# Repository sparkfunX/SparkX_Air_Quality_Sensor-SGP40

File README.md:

SparkX Air Quality Sensor - SGP40 (Qwiic)
========================================

[*SparkX Air Quality Sensor - SGP40 (Qwiic) (SPX-17729)*](https://www.sparkfun.com/products/17729)

The SGP40 is a digital gas sensor designed for easy integration into air purifiers or demand-controlled ventilation systems.
Sensirion’s CMOSens® technology offers a complete, easy to use sensor system on a single chip featuring a digital
I<sup>2</sup>C interface and a temperature controlled micro hotplate, providing a humidity compensated VOC based indoor air quality signal.
The output signal can be directly processed by Sensirion’s powerful VOC Algorithm to translate the raw signal into a VOC Index as a robust
measure for indoor air quality. The VOC Algorithm automatically adapts to the environment the sensor is exposed to. Both sensing element and
VOC Algorithm feature an unmatched robustness against contaminating gases present in real world applications enabling a unique long term
stability as well as low drift and device to device variation.

Repository Contents
-------------------
* **/Documents** - datasheets etc.
* **/Hardware** - Eagle design files (.brd, .sch)

Documentation
--------------
* **[SGP40 Arduino Library](https://github.com/sparkfun/SparkFun_SGP40_Arduino_Library)** - Arduino library for the SparkFun Air Quality Sensor - SGP40.
* **[Hookup Guide]()** - Basic hookup guide for the SparkFun Air Quality Sensor - SGP40.

Product Versions
----------------
* [SPX-17729](https://www.sparkfun.com/products/17729) - Original SparkX Release.

License Information
-------------------

This product is _**open source**_!

Please review the LICENSE.md file for license information.

If you have any questions or concerns on licensing, please contact technical support on our [SparkFun forums](https://forum.sparkfun.com/viewforum.php?f=152).

Distributed as-is; no warranty is given.

- Your friends at SparkFun.

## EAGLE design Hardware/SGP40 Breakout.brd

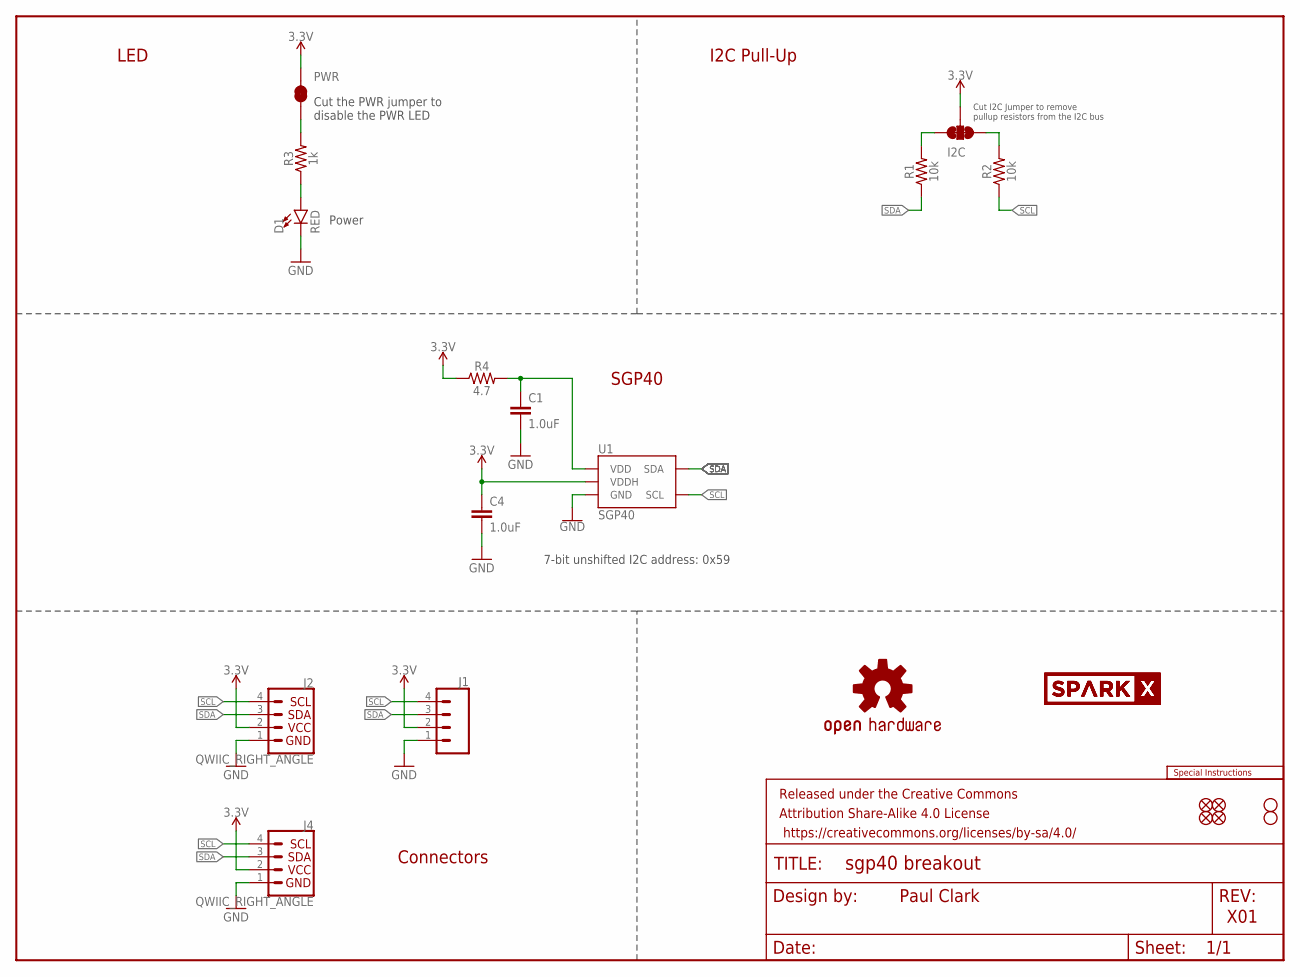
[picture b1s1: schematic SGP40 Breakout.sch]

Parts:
C1, C4: 1.0uF; 0603
D1: RED; LED-0603
FRAME1: FRAME-LETTER; CREATIVE_COMMONS
I2C: JUMPER-SMT_3_2-NC_TRACE_SILK; SMT-JUMPER_3_2-NC_TRACE_SILK
J1: CONN_041X04_NO_SILK; 1X04_NO_SILK
J2, J4: QWIIC_RIGHT_ANGLE; JST04_1MM_RA
JP1, JP2, JP5, JP6: FIDUCIALUFIDUCIAL; MICRO-FIDUCIAL
JP3, JP4: STAND-OFF
LOGO1: SPECIAL_INSTRUCTIONS-ORDERING; ORDERING_INSTRUCTIONS
LOGO5: OSHW-LOGOS; OSHW-LOGO-S
PWR: JUMPER-SMT_2_NC_TRACE_SILK; SMT-JUMPER_2_NC_TRACE_SILK
R1, R2: 10k; 0603
R3: 1k; 0603
R4: 4.7; 0603
U1: SGP40
U$10, U$18: SPARKX-LOGO3; SPARKX-SMALL

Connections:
3.3V: C4.1, I2C.2, J1.2, J2.2, J4.2, PWR.2, R4.1, U1.5 (VDDH)
GND: C1.2, C4.2, D1.C, J1.1, J2.1, J4.1, U1.2 (GND), U1.4 (GND), U1.DIEPAD (GND)
unnamed: PWR.1, R3.2
unnamed: I2C.3, R1.2
unnamed: D1.A, R3.1
unnamed: I2C.1, R2.2
unnamed: C1.1, R4.2, U1.1 (VDD)
SCL: J1.4, J2.4, J4.4, R2.1, U1.6 (SCL)
SDA: J1.3, J2.3, J4.3, R1.1, U1.3 (SDA)

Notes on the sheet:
Paul Clark
X01
7-bit unshifted I2C address: 0x59
Power
I2C Pull-Up
SGP40
Connectors
Cut the PWR jumper to disable the PWR LED
Cut I2C Jumper to remove pullup resistors from the I2C bus
LED

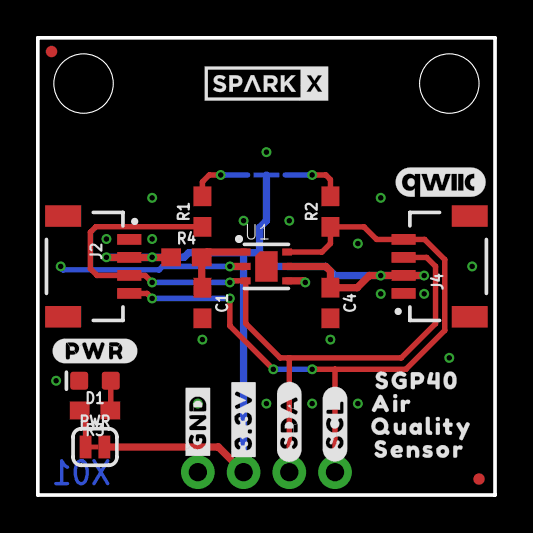
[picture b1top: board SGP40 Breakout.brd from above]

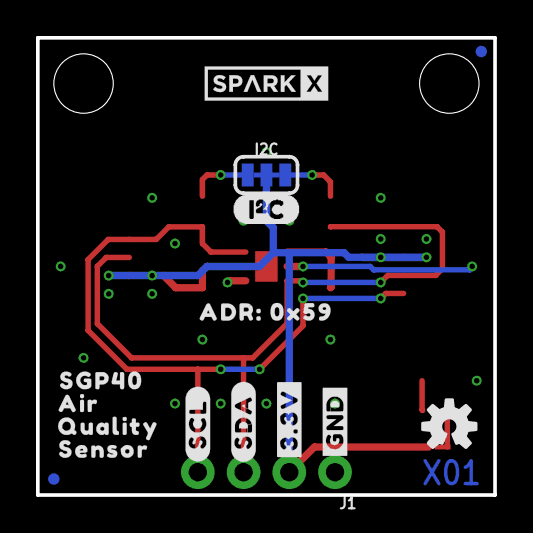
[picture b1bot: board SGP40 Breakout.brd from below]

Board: 4 copper layers, 25.4 x 25.4 mm, 44 parts (16 on the bottom side), 9 nets.

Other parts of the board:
U$1, U$33: #GND#0
U$2, U$34: #3#3V#0
U$3, U$35: #SDA#0
U$4, U$36: #SCL#0
U$15: I2C
U$16: QWIIC_5MM
U$19, U$20: SGP400
U$23, U$24: AIR0
U$25, U$28: QUALITY0
U$29, U$30: SENSOR0
U$31: ADR#_0X590
U$32: #PWR#0

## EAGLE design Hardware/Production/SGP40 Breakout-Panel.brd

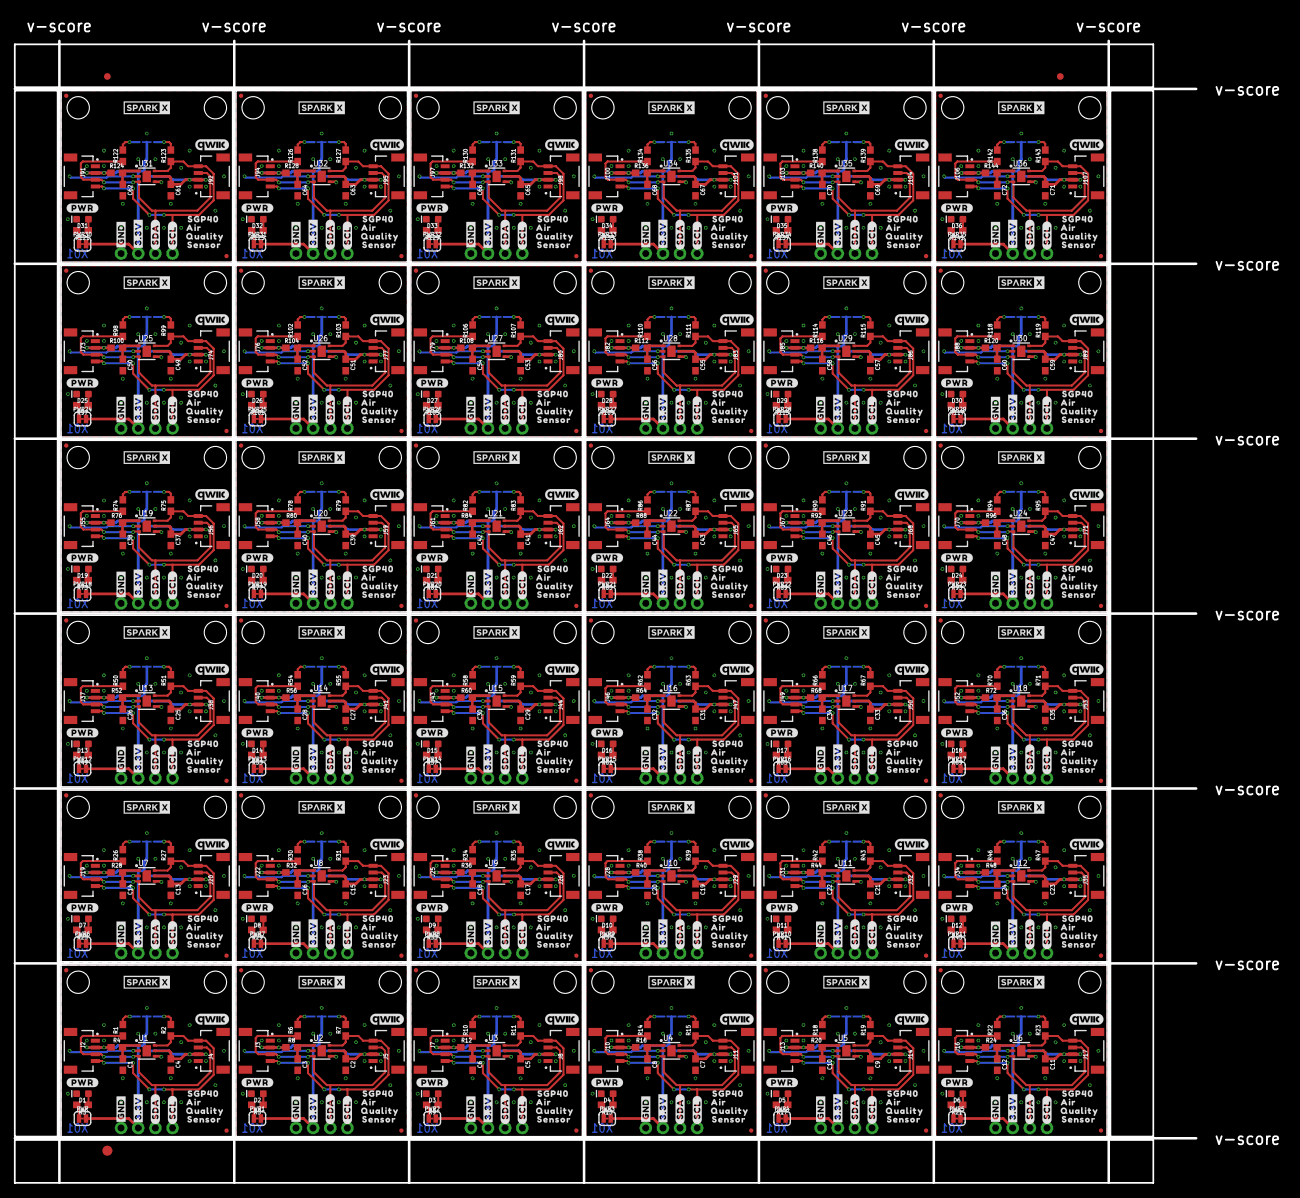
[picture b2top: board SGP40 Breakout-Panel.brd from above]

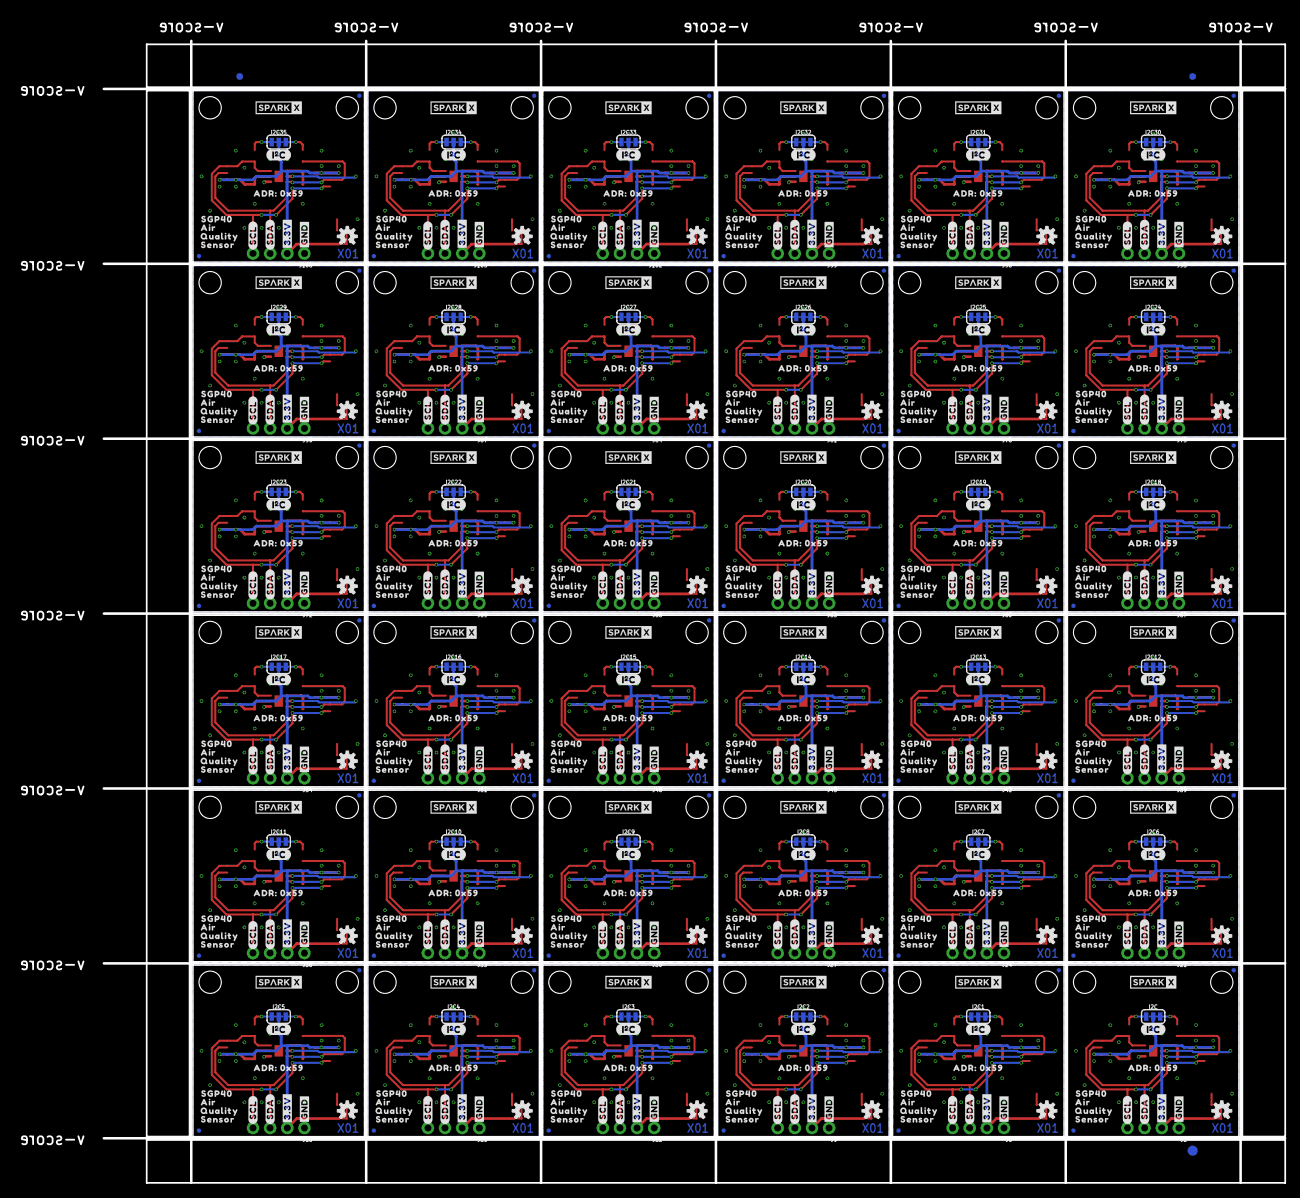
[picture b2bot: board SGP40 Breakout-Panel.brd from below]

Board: 4 copper layers, 175.0 x 169.2 mm, 1518 parts (579 on the bottom side), 324 nets.

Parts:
C1, C2, C3, C4, C5, C6, C7, C8, C9, C10, C11, C12, C13, C14, C15, C16, C17, C18, C19, C20, C21, C22, C23, C24, C25, C26, C27, C28, C29, C30, C31, C32, C33, C34, C35, C36, C37, C38, C39, C40, C41, C42, C43, C44, C45, C46, C47, C48, C49, C50, C51, C52, C53, C54, C55, C56, C57, C58, C59, C60, C61, C62, C63, C64, C65, C66, C67, C68, C69, C70, C71, C72: 1.0uF; 0603
D1, D2, D3, D4, D5, D6, D7, D8, D9, D10, D11, D12, D13, D14, D15, D16, D17, D18, D19, D20, D21, D22, D23, D24, D25, D26, D27, D28, D29, D30, D31, D32, D33, D34, D35, D36: RED; LED-0603
E$1, E$2, E$3, E$4: FIDUCIAL-1X2
E$5, E$6: FIDUCIAL-1.5X3
I2C, I2C1, I2C2, I2C3, I2C4, I2C5, I2C6, I2C7, I2C8, I2C9, I2C10, I2C11, I2C12, I2C13, I2C14, I2C15, I2C16, I2C17, I2C18, I2C19, I2C20, I2C21, I2C22, I2C23, I2C24, I2C25, I2C26, I2C27, I2C28, I2C29, I2C30, I2C31, I2C32, I2C33, I2C34, I2C35: JUMPER-SMT_3_2-NC_TRACE_SILK; SMT-JUMPER_3_2-NC_TRACE_SILK
J1, J6, J9, J12, J15, J18, J21, J24, J27, J30, J33, J36, J39, J42, J45, J48, J51, J54, J57, J60, J63, J66, J69, J72, J75, J78, J81, J84, J87, J90, J93, J96, J99, J102, J105, J108: 1X04_NO_SILK
J2, J3, J4, J5, J7, J8, J10, J11, J13, J14, J16, J17, J19, J20, J22, J23, J25, J26, J28, J29, J31, J32, J34, J35, J37, J38, J40, J41, J43, J44, J46, J47, J49, J50, J52, J53, J55, J56, J58, J59, J61, J62, J64, J65, J67, J68, J70, J71, J73, J74, J76, J77, J79, J80, J82, J83, J85, J86, J88, J89, J91, J92, J94, J95, J97, J98, J100, J101, J103, J104, J106, J107: QWIIC_RIGHT_ANGLE; JST04_1MM_RA
JP1, JP2, JP5, JP6, JP9, JP10, JP11, JP12, JP15, JP16, JP17, JP18, JP21, JP22, JP23, JP24, JP27, JP28, JP29, JP30, JP33, JP34, JP35, JP36, JP39, JP40, JP41, JP42, JP45, JP46, JP47, JP48, JP51, JP52, JP53, JP54, JP57, JP58, JP59, JP60, JP63, JP64, JP65, JP66, JP69, JP70, JP71, JP72, JP75, JP76, JP77, JP78, JP81, JP82, JP83, JP84, JP87, JP88, JP89, JP90, JP93, JP94, JP95, JP96, JP99, JP100, JP101, JP102, JP105, JP106, JP107, JP108, JP111, JP112, JP113, JP114, JP117, JP118, JP119, JP120, JP123, JP124, JP125, JP126, JP129, JP130, JP131, JP132, JP135, JP136, JP137, JP138, JP141, JP142, JP143, JP144, JP147, JP148, JP149, JP150, JP153, JP154, JP155, JP156, JP159, JP160, JP161, JP162, JP165, JP166, JP167, JP168, JP171, JP172, JP173, JP174, JP177, JP178, JP179, JP180, JP183, JP184, JP185, JP186, JP189, JP190, JP191, JP192, JP195, JP196, JP197, JP198, JP201, JP202, JP203, JP204, JP207, JP208, JP209, JP210, JP213, JP214, JP215, JP216: FIDUCIALUFIDUCIAL; MICRO-FIDUCIAL
JP3, JP4, JP7, JP8, JP13, JP14, JP19, JP20, JP25, JP26, JP31, JP32, JP37, JP38, JP43, JP44, JP49, JP50, JP55, JP56, JP61, JP62, JP67, JP68, JP73, JP74, JP79, JP80, JP85, JP86, JP91, JP92, JP97, JP98, JP103, JP104, JP109, JP110, JP115, JP116, JP121, JP122, JP127, JP128, JP133, JP134, JP139, JP140, JP145, JP146, JP151, JP152, JP157, JP158, JP163, JP164, JP169, JP170, JP175, JP176, JP181, JP182, JP187, JP188, JP193, JP194, JP199, JP200, JP205, JP206, JP211, JP212: STAND-OFF
LOGO1, LOGO2, LOGO3, LOGO4, LOGO5, LOGO6, LOGO7, LOGO8, LOGO9, LOGO10, LOGO11, LOGO12, LOGO13, LOGO14, LOGO15, LOGO16, LOGO17, LOGO18, LOGO19, LOGO20, LOGO21, LOGO22, LOGO23, LOGO24, LOGO25, LOGO26, LOGO27, LOGO28, LOGO29, LOGO30, LOGO31, LOGO32, LOGO33, LOGO34, LOGO35, LOGO36: OSHW-LOGOS; OSHW-LOGO-S
PWR, PWR1, PWR2, PWR3, PWR4, PWR5, PWR6, PWR7, PWR8, PWR9, PWR10, PWR11, PWR12, PWR13, PWR14, PWR15, PWR16, PWR17, PWR18, PWR19, PWR20, PWR21, PWR22, PWR23, PWR24, PWR25, PWR26, PWR27, PWR28, PWR29, PWR30, PWR31, PWR32, PWR33, PWR34, PWR35: JUMPER-SMT_2_NC_TRACE_SILK; SMT-JUMPER_2_NC_TRACE_SILK
R1, R2, R6, R7, R10, R11, R14, R15, R18, R19, R22, R23, R26, R27, R30, R31, R34, R35, R38, R39, R42, R43, R46, R47, R50, R51, R54, R55, R58, R59, R62, R63, R66, R67, R70, R71, R74, R75, R78, R79, R82, R83, R86, R87, R90, R91, R94, R95, R98, R99, R102, R103, R106, R107, R110, R111, R114, R115, R118, R119, R122, R123, R126, R127, R130, R131, R134, R135, R138, R139, R142, R143: 10k; 0603
R3, R5, R9, R13, R17, R21, R25, R29, R33, R37, R41, R45, R49, R53, R57, R61, R65, R69, R73, R77, R81, R85, R89, R93, R97, R101, R105, R109, R113, R117, R121, R125, R129, R133, R137, R141: 1k; 0603
R4, R8, R12, R16, R20, R24, R28, R32, R36, R40, R44, R48, R52, R56, R60, R64, R68, R72, R76, R80, R84, R88, R92, R96, R100, R104, R108, R112, R116, R120, R124, R128, R132, R136, R140, R144: 4.7; 0603
U1, U2, U3, U4, U5, U6, U7, U8, U9, U10, U11, U12, U13, U14, U15, U16, U17, U18, U19, U20, U21, U22, U23, U24, U25, U26, U27, U28, U29, U30, U31, U32, U33, U34, U35, U36: SGP40
U$1, U$33, U$37, U$41, U$59, U$63, U$81, U$85, U$103, U$107, U$125, U$129, U$147, U$151, U$169, U$173, U$191, U$195, U$213, U$217, U$235, U$239, U$257, U$261, U$279, U$283, U$301, U$305, U$323, U$327, U$345, U$349, U$367, U$371, U$389, U$393, U$411, U$415, U$433, U$437, U$455, U$459, U$477, U$481, U$499, U$503, U$521, U$525, U$543, U$547, U$565, U$569, U$587, U$591, U$609, U$613, U$631, U$635, U$653, U$657, U$675, U$679, U$697, U$701, U$719, U$723, U$741, U$745, U$763, U$767, U$785, U$789: #GND#0
U$2, U$34, U$38, U$42, U$60, U$64, U$82, U$86, U$104, U$108, U$126, U$130, U$148, U$152, U$170, U$174, U$192, U$196, U$214, U$218, U$236, U$240, U$258, U$262, U$280, U$284, U$302, U$306, U$324, U$328, U$346, U$350, U$368, U$372, U$390, U$394, U$412, U$416, U$434, U$438, U$456, U$460, U$478, U$482, U$500, U$504, U$522, U$526, U$544, U$548, U$566, U$570, U$588, U$592, U$610, U$614, U$632, U$636, U$654, U$658, U$676, U$680, U$698, U$702, U$720, U$724, U$742, U$746, U$764, U$768, U$786, U$790: #3#3V#0
U$3, U$35, U$39, U$43, U$61, U$65, U$83, U$87, U$105, U$109, U$127, U$131, U$149, U$153, U$171, U$175, U$193, U$197, U$215, U$219, U$237, U$241, U$259, U$263, U$281, U$285, U$303, U$307, U$325, U$329, U$347, U$351, U$369, U$373, U$391, U$395, U$413, U$417, U$435, U$439, U$457, U$461, U$479, U$483, U$501, U$505, U$523, U$527, U$545, U$549, U$567, U$571, U$589, U$593, U$611, U$615, U$633, U$637, U$655, U$659, U$677, U$681, U$699, U$703, U$721, U$725, U$743, U$747, U$765, U$769, U$787, U$791: #SDA#0
U$4, U$36, U$40, U$44, U$62, U$66, U$84, U$88, U$106, U$110, U$128, U$132, U$150, U$154, U$172, U$176, U$194, U$198, U$216, U$220, U$238, U$242, U$260, U$264, U$282, U$286, U$304, U$308, U$326, U$330, U$348, U$352, U$370, U$374, U$392, U$396, U$414, U$418, U$436, U$440, U$458, U$462, U$480, U$484, U$502, U$506, U$524, U$528, U$546, U$550, U$568, U$572, U$590, U$594, U$612, U$616, U$634, U$638, U$656, U$660, U$678, U$682, U$700, U$704, U$722, U$726, U$744, U$748, U$766, U$770, U$788, U$792: #SCL#0
U$5, U$15, U$45, U$67, U$89, U$111, U$133, U$155, U$177, U$199, U$221, U$243, U$265, U$287, U$309, U$331, U$353, U$375, U$397, U$419, U$441, U$463, U$485, U$507, U$529, U$551, U$573, U$595, U$617, U$639, U$661, U$683, U$705, U$727, U$749, U$771: I2C
U$6, U$16, U$46, U$68, U$90, U$112, U$134, U$156, U$178, U$200, U$222, U$244, U$266, U$288, U$310, U$332, U$354, U$376, U$398, U$420, U$442, U$464, U$486, U$508, U$530, U$552, U$574, U$596, U$618, U$640, U$662, U$684, U$706, U$728, U$750, U$772: QWIIC_5MM
U$7, U$8, U$10, U$18, U$47, U$48, U$69, U$70, U$91, U$92, U$113, U$114, U$135, U$136, U$157, U$158, U$179, U$180, U$201, U$202, U$223, U$224, U$245, U$246, U$267, U$268, U$289, U$290, U$311, U$312, U$333, U$334, U$355, U$356, U$377, U$378, U$399, U$400, U$421, U$422, U$443, U$444, U$465, U$466, U$487, U$488, U$509, U$510, U$531, U$532, U$553, U$554, U$575, U$576, U$597, U$598, U$619, U$620, U$641, U$642, U$663, U$664, U$685, U$686, U$707, U$708, U$729, U$730, U$751, U$752, U$773, U$774: SPARKX-LOGO3; SPARKX-SMALL
U$9, U$11, U$19, U$20, U$49, U$50, U$71, U$72, U$93, U$94, U$115, U$116, U$137, U$138, U$159, U$160, U$181, U$182, U$203, U$204, U$225, U$226, U$247, U$248, U$269, U$270, U$291, U$292, U$313, U$314, U$335, U$336, U$357, U$358, U$379, U$380, U$401, U$402, U$423, U$424, U$445, U$446, U$467, U$468, U$489, U$490, U$511, U$512, U$533, U$534, U$555, U$556, U$577, U$578, U$599, U$600, U$621, U$622, U$643, U$644, U$665, U$666, U$687, U$688, U$709, U$710, U$731, U$732, U$753, U$754, U$775, U$776: SGP400
U$12, U$13, U$23, U$24, U$51, U$52, U$73, U$74, U$95, U$96, U$117, U$118, U$139, U$140, U$161, U$162, U$183, U$184, U$205, U$206, U$227, U$228, U$249, U$250, U$271, U$272, U$293, U$294, U$315, U$316, U$337, U$338, U$359, U$360, U$381, U$382, U$403, U$404, U$425, U$426, U$447, U$448, U$469, U$470, U$491, U$492, U$513, U$514, U$535, U$536, U$557, U$558, U$579, U$580, U$601, U$602, U$623, U$624, U$645, U$646, U$667, U$668, U$689, U$690, U$711, U$712, U$733, U$734, U$755, U$756, U$777, U$778: AIR0
U$14, U$17, U$25, U$28, U$53, U$54, U$75, U$76, U$97, U$98, U$119, U$120, U$141, U$142, U$163, U$164, U$185, U$186, U$207, U$208, U$229, U$230, U$251, U$252, U$273, U$274, U$295, U$296, U$317, U$318, U$339, U$340, U$361, U$362, U$383, U$384, U$405, U$406, U$427, U$428, U$449, U$450, U$471, U$472, U$493, U$494, U$515, U$516, U$537, U$538, U$559, U$560, U$581, U$582, U$603, U$604, U$625, U$626, U$647, U$648, U$669, U$670, U$691, U$692, U$713, U$714, U$735, U$736, U$757, U$758, U$779, U$780: QUALITY0
U$21, U$22, U$29, U$30, U$55, U$56, U$77, U$78, U$99, U$100, U$121, U$122, U$143, U$144, U$165, U$166, U$187, U$188, U$209, U$210, U$231, U$232, U$253, U$254, U$275, U$276, U$297, U$298, U$319, U$320, U$341, U$342, U$363, U$364, U$385, U$386, U$407, U$408, U$429, U$430, U$451, U$452, U$473, U$474, U$495, U$496, U$517, U$518, U$539, U$540, U$561, U$562, U$583, U$584, U$605, U$606, U$627, U$628, U$649, U$650, U$671, U$672, U$693, U$694, U$715, U$716, U$737, U$738, U$759, U$760, U$781, U$782: SENSOR0
U$26, U$31, U$57, U$79, U$101, U$123, U$145, U$167, U$189, U$211, U$233, U$255, U$277, U$299, U$321, U$343, U$365, U$387, U$409, U$431, U$453, U$475, U$497, U$519, U$541, U$563, U$585, U$607, U$629, U$651, U$673, U$695, U$717, U$739, U$761, U$783: ADR#_0X590
U$27, U$32, U$58, U$80, U$102, U$124, U$146, U$168, U$190, U$212, U$234, U$256, U$278, U$300, U$322, U$344, U$366, U$388, U$410, U$432, U$454, U$476, U$498, U$520, U$542, U$564, U$586, U$608, U$630, U$652, U$674, U$696, U$718, U$740, U$762, U$784: #PWR#0

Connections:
3.3V: C4.1, I2C.2, J1.2, J2.2, J4.2, PWR.2, R4.1, U1.5
3.3V1: C2.1, I2C1.2, J3.2, J5.2, J6.2, PWR1.2, R8.1, U2.5
3.3V2: C5.1, I2C2.2, J7.2, J8.2, J9.2, PWR2.2, R12.1, U3.5
3.3V3: C7.1, I2C3.2, J10.2, J11.2, J12.2, PWR3.2, R16.1, U4.5
3.3V4: C9.1, I2C4.2, J13.2, J14.2, J15.2, PWR4.2, R20.1, U5.5
3.3V5: C11.1, I2C5.2, J16.2, J17.2, J18.2, PWR5.2, R24.1, U6.5
3.3V6: C13.1, I2C6.2, J19.2, J20.2, J21.2, PWR6.2, R28.1, U7.5
3.3V7: C15.1, I2C7.2, J22.2, J23.2, J24.2, PWR7.2, R32.1, U8.5
3.3V8: C17.1, I2C8.2, J25.2, J26.2, J27.2, PWR8.2, R36.1, U9.5
3.3V9: C19.1, I2C9.2, J28.2, J29.2, J30.2, PWR9.2, R40.1, U10.5
3.3V10: C21.1, I2C10.2, J31.2, J32.2, J33.2, PWR10.2, R44.1, U11.5
3.3V11: C23.1, I2C11.2, J34.2, J35.2, J36.2, PWR11.2, R48.1, U12.5
3.3V12: C25.1, I2C12.2, J37.2, J38.2, J39.2, PWR12.2, R52.1, U13.5
3.3V13: C27.1, I2C13.2, J40.2, J41.2, J42.2, PWR13.2, R56.1, U14.5
3.3V14: C29.1, I2C14.2, J43.2, J44.2, J45.2, PWR14.2, R60.1, U15.5
3.3V15: C31.1, I2C15.2, J46.2, J47.2, J48.2, PWR15.2, R64.1, U16.5
3.3V16: C33.1, I2C16.2, J49.2, J50.2, J51.2, PWR16.2, R68.1, U17.5
3.3V17: C35.1, I2C17.2, J52.2, J53.2, J54.2, PWR17.2, R72.1, U18.5
3.3V18: C37.1, I2C18.2, J55.2, J56.2, J57.2, PWR18.2, R76.1, U19.5
3.3V19: C39.1, I2C19.2, J58.2, J59.2, J60.2, PWR19.2, R80.1, U20.5
3.3V20: C41.1, I2C20.2, J61.2, J62.2, J63.2, PWR20.2, R84.1, U21.5
3.3V21: C43.1, I2C21.2, J64.2, J65.2, J66.2, PWR21.2, R88.1, U22.5
3.3V22: C45.1, I2C22.2, J67.2, J68.2, J69.2, PWR22.2, R92.1, U23.5
3.3V23: C47.1, I2C23.2, J70.2, J71.2, J72.2, PWR23.2, R96.1, U24.5
3.3V24: C49.1, I2C24.2, J73.2, J74.2, J75.2, PWR24.2, R100.1, U25.5
3.3V25: C51.1, I2C25.2, J76.2, J77.2, J78.2, PWR25.2, R104.1, U26.5
3.3V26: C53.1, I2C26.2, J79.2, J80.2, J81.2, PWR26.2, R108.1, U27.5
3.3V27: C55.1, I2C27.2, J82.2, J83.2, J84.2, PWR27.2, R112.1, U28.5
3.3V28: C57.1, I2C28.2, J85.2, J86.2, J87.2, PWR28.2, R116.1, U29.5
3.3V29: C59.1, I2C29.2, J88.2, J89.2, J90.2, PWR29.2, R120.1, U30.5
3.3V30: C61.1, I2C30.2, J91.2, J92.2, J93.2, PWR30.2, R124.1, U31.5
3.3V31: C63.1, I2C31.2, J94.2, J95.2, J96.2, PWR31.2, R128.1, U32.5
3.3V32: C65.1, I2C32.2, J97.2, J98.2, J99.2, PWR32.2, R132.1, U33.5
3.3V33: C67.1, I2C33.2, J100.2, J101.2, J102.2, PWR33.2, R136.1, U34.5
3.3V34: C69.1, I2C34.2, J103.2, J104.2, J105.2, PWR34.2, R140.1, U35.5
3.3V35: C71.1, I2C35.2, J106.2, J107.2, J108.2, PWR35.2, R144.1, U36.5
GND: C1.2, C4.2, D1.C, J1.1, J2.1, J4.1, U1.2, U1.4, U1.DIEPAD
GND1: C2.2, C3.2, D2.C, J3.1, J5.1, J6.1, U2.2, U2.4, U2.DIEPAD
GND2: C5.2, C6.2, D3.C, J7.1, J8.1, J9.1, U3.2, U3.4, U3.DIEPAD
GND3: C7.2, C8.2, D4.C, J10.1, J11.1, J12.1, U4.2, U4.4, U4.DIEPAD
GND4: C9.2, C10.2, D5.C, J13.1, J14.1, J15.1, U5.2, U5.4, U5.DIEPAD
GND5: C11.2, C12.2, D6.C, J16.1, J17.1, J18.1, U6.2, U6.4, U6.DIEPAD
GND6: C13.2, C14.2, D7.C, J19.1, J20.1, J21.1, U7.2, U7.4, U7.DIEPAD
GND7: C15.2, C16.2, D8.C, J22.1, J23.1, J24.1, U8.2, U8.4, U8.DIEPAD
GND8: C17.2, C18.2, D9.C, J25.1, J26.1, J27.1, U9.2, U9.4, U9.DIEPAD
GND9: C19.2, C20.2, D10.C, J28.1, J29.1, J30.1, U10.2, U10.4, U10.DIEPAD
GND10: C21.2, C22.2, D11.C, J31.1, J32.1, J33.1, U11.2, U11.4, U11.DIEPAD
GND11: C23.2, C24.2, D12.C, J34.1, J35.1, J36.1, U12.2, U12.4, U12.DIEPAD
GND12: C25.2, C26.2, D13.C, J37.1, J38.1, J39.1, U13.2, U13.4, U13.DIEPAD
GND13: C27.2, C28.2, D14.C, J40.1, J41.1, J42.1, U14.2, U14.4, U14.DIEPAD
GND14: C29.2, C30.2, D15.C, J43.1, J44.1, J45.1, U15.2, U15.4, U15.DIEPAD
GND15: C31.2, C32.2, D16.C, J46.1, J47.1, J48.1, U16.2, U16.4, U16.DIEPAD
GND16: C33.2, C34.2, D17.C, J49.1, J50.1, J51.1, U17.2, U17.4, U17.DIEPAD
GND17: C35.2, C36.2, D18.C, J52.1, J53.1, J54.1, U18.2, U18.4, U18.DIEPAD
GND18: C37.2, C38.2, D19.C, J55.1, J56.1, J57.1, U19.2, U19.4, U19.DIEPAD
GND19: C39.2, C40.2, D20.C, J58.1, J59.1, J60.1, U20.2, U20.4, U20.DIEPAD
GND20: C41.2, C42.2, D21.C, J61.1, J62.1, J63.1, U21.2, U21.4, U21.DIEPAD
GND21: C43.2, C44.2, D22.C, J64.1, J65.1, J66.1, U22.2, U22.4, U22.DIEPAD
GND22: C45.2, C46.2, D23.C, J67.1, J68.1, J69.1, U23.2, U23.4, U23.DIEPAD
GND23: C47.2, C48.2, D24.C, J70.1, J71.1, J72.1, U24.2, U24.4, U24.DIEPAD
GND24: C49.2, C50.2, D25.C, J73.1, J74.1, J75.1, U25.2, U25.4, U25.DIEPAD
GND25: C51.2, C52.2, D26.C, J76.1, J77.1, J78.1, U26.2, U26.4, U26.DIEPAD
GND26: C53.2, C54.2, D27.C, J79.1, J80.1, J81.1, U27.2, U27.4, U27.DIEPAD
GND27: C55.2, C56.2, D28.C, J82.1, J83.1, J84.1, U28.2, U28.4, U28.DIEPAD
GND28: C57.2, C58.2, D29.C, J85.1, J86.1, J87.1, U29.2, U29.4, U29.DIEPAD
GND29: C59.2, C60.2, D30.C, J88.1, J89.1, J90.1, U30.2, U30.4, U30.DIEPAD
GND30: C61.2, C62.2, D31.C, J91.1, J92.1, J93.1, U31.2, U31.4, U31.DIEPAD
GND31: C63.2, C64.2, D32.C, J94.1, J95.1, J96.1, U32.2, U32.4, U32.DIEPAD
GND32: C65.2, C66.2, D33.C, J97.1, J98.1, J99.1, U33.2, U33.4, U33.DIEPAD
GND33: C67.2, C68.2, D34.C, J100.1, J101.1, J102.1, U34.2, U34.4, U34.DIEPAD
GND34: C69.2, C70.2, D35.C, J103.1, J104.1, J105.1, U35.2, U35.4, U35.DIEPAD
GND35: C71.2, C72.2, D36.C, J106.1, J107.1, J108.1, U36.2, U36.4, U36.DIEPAD
unnamed: PWR.1, R3.2
unnamed: I2C.3, R1.2
unnamed: D1.A, R3.1
unnamed: I2C.1, R2.2
unnamed: C1.1, R4.2, U1.1
unnamed: D2.A, R5.1
unnamed: PWR1.1, R5.2
unnamed: I2C1.3, R6.2
unnamed: I2C1.1, R7.2
unnamed: C3.1, R8.2, U2.1
unnamed: D3.A, R9.1
unnamed: PWR2.1, R9.2
unnamed: I2C2.3, R10.2
unnamed: I2C2.1, R11.2
unnamed: C6.1, R12.2, U3.1
unnamed: D4.A, R13.1
unnamed: PWR3.1, R13.2
unnamed: I2C3.3, R14.2
unnamed: I2C3.1, R15.2
unnamed: C8.1, R16.2, U4.1
unnamed: D5.A, R17.1
unnamed: PWR4.1, R17.2
unnamed: I2C4.3, R18.2
unnamed: I2C4.1, R19.2
unnamed: C10.1, R20.2, U5.1
unnamed: D6.A, R21.1
unnamed: PWR5.1, R21.2
unnamed: I2C5.3, R22.2
unnamed: I2C5.1, R23.2
unnamed: C12.1, R24.2, U6.1
unnamed: D7.A, R25.1
unnamed: PWR6.1, R25.2
unnamed: I2C6.3, R26.2
unnamed: I2C6.1, R27.2
unnamed: C14.1, R28.2, U7.1
unnamed: D8.A, R29.1
unnamed: PWR7.1, R29.2
unnamed: I2C7.3, R30.2
unnamed: I2C7.1, R31.2
unnamed: C16.1, R32.2, U8.1
unnamed: D9.A, R33.1
unnamed: PWR8.1, R33.2
unnamed: I2C8.3, R34.2
unnamed: I2C8.1, R35.2
unnamed: C18.1, R36.2, U9.1
unnamed: D10.A, R37.1
unnamed: PWR9.1, R37.2
unnamed: I2C9.3, R38.2
unnamed: I2C9.1, R39.2
unnamed: C20.1, R40.2, U10.1
unnamed: D11.A, R41.1
unnamed: PWR10.1, R41.2
unnamed: I2C10.3, R42.2
unnamed: I2C10.1, R43.2
unnamed: C22.1, R44.2, U11.1
unnamed: D12.A, R45.1
unnamed: PWR11.1, R45.2
unnamed: I2C11.3, R46.2
unnamed: I2C11.1, R47.2
unnamed: C24.1, R48.2, U12.1
unnamed: D13.A, R49.1
unnamed: PWR12.1, R49.2
unnamed: I2C12.3, R50.2
unnamed: I2C12.1, R51.2
unnamed: C26.1, R52.2, U13.1
unnamed: D14.A, R53.1
unnamed: PWR13.1, R53.2
unnamed: I2C13.3, R54.2
unnamed: I2C13.1, R55.2
unnamed: C28.1, R56.2, U14.1
unnamed: D15.A, R57.1
unnamed: PWR14.1, R57.2
unnamed: I2C14.3, R58.2
unnamed: I2C14.1, R59.2
unnamed: C30.1, R60.2, U15.1
unnamed: D16.A, R61.1
unnamed: PWR15.1, R61.2
unnamed: I2C15.3, R62.2
unnamed: I2C15.1, R63.2
unnamed: C32.1, R64.2, U16.1
unnamed: D17.A, R65.1
unnamed: PWR16.1, R65.2
unnamed: I2C16.3, R66.2
unnamed: I2C16.1, R67.2
unnamed: C34.1, R68.2, U17.1
unnamed: D18.A, R69.1
unnamed: PWR17.1, R69.2
unnamed: I2C17.3, R70.2
unnamed: I2C17.1, R71.2
unnamed: C36.1, R72.2, U18.1
unnamed: D19.A, R73.1
unnamed: PWR18.1, R73.2
unnamed: I2C18.3, R74.2
unnamed: I2C18.1, R75.2
unnamed: C38.1, R76.2, U19.1
unnamed: D20.A, R77.1
unnamed: PWR19.1, R77.2
unnamed: I2C19.3, R78.2
unnamed: I2C19.1, R79.2
unnamed: C40.1, R80.2, U20.1
unnamed: D21.A, R81.1
unnamed: PWR20.1, R81.2
unnamed: I2C20.3, R82.2
unnamed: I2C20.1, R83.2
unnamed: C42.1, R84.2, U21.1
unnamed: D22.A, R85.1
unnamed: PWR21.1, R85.2
unnamed: I2C21.3, R86.2
unnamed: I2C21.1, R87.2
unnamed: C44.1, R88.2, U22.1
unnamed: D23.A, R89.1
unnamed: PWR22.1, R89.2
unnamed: I2C22.3, R90.2
unnamed: I2C22.1, R91.2
unnamed: C46.1, R92.2, U23.1
unnamed: D24.A, R93.1
unnamed: PWR23.1, R93.2
unnamed: I2C23.3, R94.2
unnamed: I2C23.1, R95.2
unnamed: C48.1, R96.2, U24.1
unnamed: D25.A, R97.1
unnamed: PWR24.1, R97.2
unnamed: I2C24.3, R98.2
unnamed: I2C24.1, R99.2
unnamed: C50.1, R100.2, U25.1
unnamed: D26.A, R101.1
unnamed: PWR25.1, R101.2
unnamed: I2C25.3, R102.2
unnamed: I2C25.1, R103.2
unnamed: C52.1, R104.2, U26.1
unnamed: D27.A, R105.1
unnamed: PWR26.1, R105.2
unnamed: I2C26.3, R106.2
unnamed: I2C26.1, R107.2
unnamed: C54.1, R108.2, U27.1
unnamed: D28.A, R109.1
unnamed: PWR27.1, R109.2
unnamed: I2C27.3, R110.2
unnamed: I2C27.1, R111.2
unnamed: C56.1, R112.2, U28.1
unnamed: D29.A, R113.1
unnamed: PWR28.1, R113.2
unnamed: I2C28.3, R114.2
unnamed: I2C28.1, R115.2
unnamed: C58.1, R116.2, U29.1
unnamed: D30.A, R117.1
unnamed: PWR29.1, R117.2
unnamed: I2C29.3, R118.2
unnamed: I2C29.1, R119.2
unnamed: C60.1, R120.2, U30.1
unnamed: D31.A, R121.1
unnamed: PWR30.1, R121.2
unnamed: I2C30.3, R122.2
unnamed: I2C30.1, R123.2
unnamed: C62.1, R124.2, U31.1
unnamed: D32.A, R125.1
unnamed: PWR31.1, R125.2
unnamed: I2C31.3, R126.2
unnamed: I2C31.1, R127.2
unnamed: C64.1, R128.2, U32.1
unnamed: D33.A, R129.1
unnamed: PWR32.1, R129.2
unnamed: I2C32.3, R130.2
unnamed: I2C32.1, R131.2
unnamed: C66.1, R132.2, U33.1
unnamed: D34.A, R133.1
unnamed: PWR33.1, R133.2
unnamed: I2C33.3, R134.2
unnamed: I2C33.1, R135.2
unnamed: C68.1, R136.2, U34.1
unnamed: D35.A, R137.1
unnamed: PWR34.1, R137.2
unnamed: I2C34.3, R138.2
unnamed: I2C34.1, R139.2
unnamed: C70.1, R140.2, U35.1
unnamed: D36.A, R141.1
unnamed: PWR35.1, R141.2
unnamed: I2C35.3, R142.2
unnamed: I2C35.1, R143.2
unnamed: C72.1, R144.2, U36.1
SCL: J1.4, J2.4, J4.4, R2.1, U1.6
SCL1: J3.4, J5.4, J6.4, R7.1, U2.6
SCL2: J7.4, J8.4, J9.4, R11.1, U3.6
SCL3: J10.4, J11.4, J12.4, R15.1, U4.6
SCL4: J13.4, J14.4, J15.4, R19.1, U5.6
SCL5: J16.4, J17.4, J18.4, R23.1, U6.6
SCL6: J19.4, J20.4, J21.4, R27.1, U7.6
SCL7: J22.4, J23.4, J24.4, R31.1, U8.6
SCL8: J25.4, J26.4, J27.4, R35.1, U9.6
SCL9: J28.4, J29.4, J30.4, R39.1, U10.6
SCL10: J31.4, J32.4, J33.4, R43.1, U11.6
SCL11: J34.4, J35.4, J36.4, R47.1, U12.6
SCL12: J37.4, J38.4, J39.4, R51.1, U13.6
SCL13: J40.4, J41.4, J42.4, R55.1, U14.6
SCL14: J43.4, J44.4, J45.4, R59.1, U15.6
SCL15: J46.4, J47.4, J48.4, R63.1, U16.6
SCL16: J49.4, J50.4, J51.4, R67.1, U17.6
SCL17: J52.4, J53.4, J54.4, R71.1, U18.6
SCL18: J55.4, J56.4, J57.4, R75.1, U19.6
SCL19: J58.4, J59.4, J60.4, R79.1, U20.6
SCL20: J61.4, J62.4, J63.4, R83.1, U21.6
SCL21: J64.4, J65.4, J66.4, R87.1, U22.6
SCL22: J67.4, J68.4, J69.4, R91.1, U23.6
SCL23: J70.4, J71.4, J72.4, R95.1, U24.6
SCL24: J73.4, J74.4, J75.4, R99.1, U25.6
SCL25: J76.4, J77.4, J78.4, R103.1, U26.6
SCL26: J79.4, J80.4, J81.4, R107.1, U27.6
SCL27: J82.4, J83.4, J84.4, R111.1, U28.6
SCL28: J85.4, J86.4, J87.4, R115.1, U29.6
SCL29: J88.4, J89.4, J90.4, R119.1, U30.6
SCL30: J91.4, J92.4, J93.4, R123.1, U31.6
SCL31: J94.4, J95.4, J96.4, R127.1, U32.6
SCL32: J97.4, J98.4, J99.4, R131.1, U33.6
SCL33: J100.4, J101.4, J102.4, R135.1, U34.6
SCL34: J103.4, J104.4, J105.4, R139.1, U35.6
SCL35: J106.4, J107.4, J108.4, R143.1, U36.6
SDA: J1.3, J2.3, J4.3, R1.1, U1.3
SDA1: J3.3, J5.3, J6.3, R6.1, U2.3
SDA2: J7.3, J8.3, J9.3, R10.1, U3.3
SDA3: J10.3, J11.3, J12.3, R14.1, U4.3
SDA4: J13.3, J14.3, J15.3, R18.1, U5.3
SDA5: J16.3, J17.3, J18.3, R22.1, U6.3
SDA6: J19.3, J20.3, J21.3, R26.1, U7.3
SDA7: J22.3, J23.3, J24.3, R30.1, U8.3
SDA8: J25.3, J26.3, J27.3, R34.1, U9.3
SDA9: J28.3, J29.3, J30.3, R38.1, U10.3
SDA10: J31.3, J32.3, J33.3, R42.1, U11.3
SDA11: J34.3, J35.3, J36.3, R46.1, U12.3
SDA12: J37.3, J38.3, J39.3, R50.1, U13.3
SDA13: J40.3, J41.3, J42.3, R54.1, U14.3
SDA14: J43.3, J44.3, J45.3, R58.1, U15.3
SDA15: J46.3, J47.3, J48.3, R62.1, U16.3
SDA16: J49.3, J50.3, J51.3, R66.1, U17.3
SDA17: J52.3, J53.3, J54.3, R70.1, U18.3
SDA18: J55.3, J56.3, J57.3, R74.1, U19.3
SDA19: J58.3, J59.3, J60.3, R78.1, U20.3
SDA20: J61.3, J62.3, J63.3, R82.1, U21.3
SDA21: J64.3, J65.3, J66.3, R86.1, U22.3
SDA22: J67.3, J68.3, J69.3, R90.1, U23.3
SDA23: J70.3, J71.3, J72.3, R94.1, U24.3
SDA24: J73.3, J74.3, J75.3, R98.1, U25.3
SDA25: J76.3, J77.3, J78.3, R102.1, U26.3
SDA26: J79.3, J80.3, J81.3, R106.1, U27.3
SDA27: J82.3, J83.3, J84.3, R110.1, U28.3
SDA28: J85.3, J86.3, J87.3, R114.1, U29.3
SDA29: J88.3, J89.3, J90.3, R118.1, U30.3
SDA30: J91.3, J92.3, J93.3, R122.1, U31.3
SDA31: J94.3, J95.3, J96.3, R126.1, U32.3
SDA32: J97.3, J98.3, J99.3, R130.1, U33.3
SDA33: J100.3, J101.3, J102.3, R134.1, U34.3
SDA34: J103.3, J104.3, J105.3, R138.1, U35.3
SDA35: J106.3, J107.3, J108.3, R142.1, U36.3

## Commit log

2020-12-04 Adding X01 PCB and images
2020-12-05 Adding the missing PROD_IDs. Moved schematic block titles to the Symbol layer.
2020-12-05 Adding the SKU
2021-01-25 Adding the product image
2021-03-20 Remove New-Parts. Tweak 0.3mm drill size.

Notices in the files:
parts and their libraries:
SparkFun-Resistors: Licensing: Creative Commons ShareAlike 4.0 International - https://creativecommons.org/licenses/by-sa/4.0
SparkFun-Aesthetics: Released under the Creative Commons Attribution Share-Alike 4.0 License
SparkFun-Aesthetics: https://creativecommons.org/licenses/by-sa/4.0
